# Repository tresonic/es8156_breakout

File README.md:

# ES8156 Breakout - *Untested*

Breakout PCB for the Everest Semiconductor [ES8156](http://www.everest-semi.com/pdf/ES8156%20PB.pdf), a DAC with integrated headphone driver.

----

Symbol and footprint were generated to `./lib` with [easyeda2kicad.py](https://github.com/uPesy/easyeda2kicad.py) like:

`easyeda2kicad --full --lcsc_id=C2887138 --output ./lib/lcsc_parts`

----

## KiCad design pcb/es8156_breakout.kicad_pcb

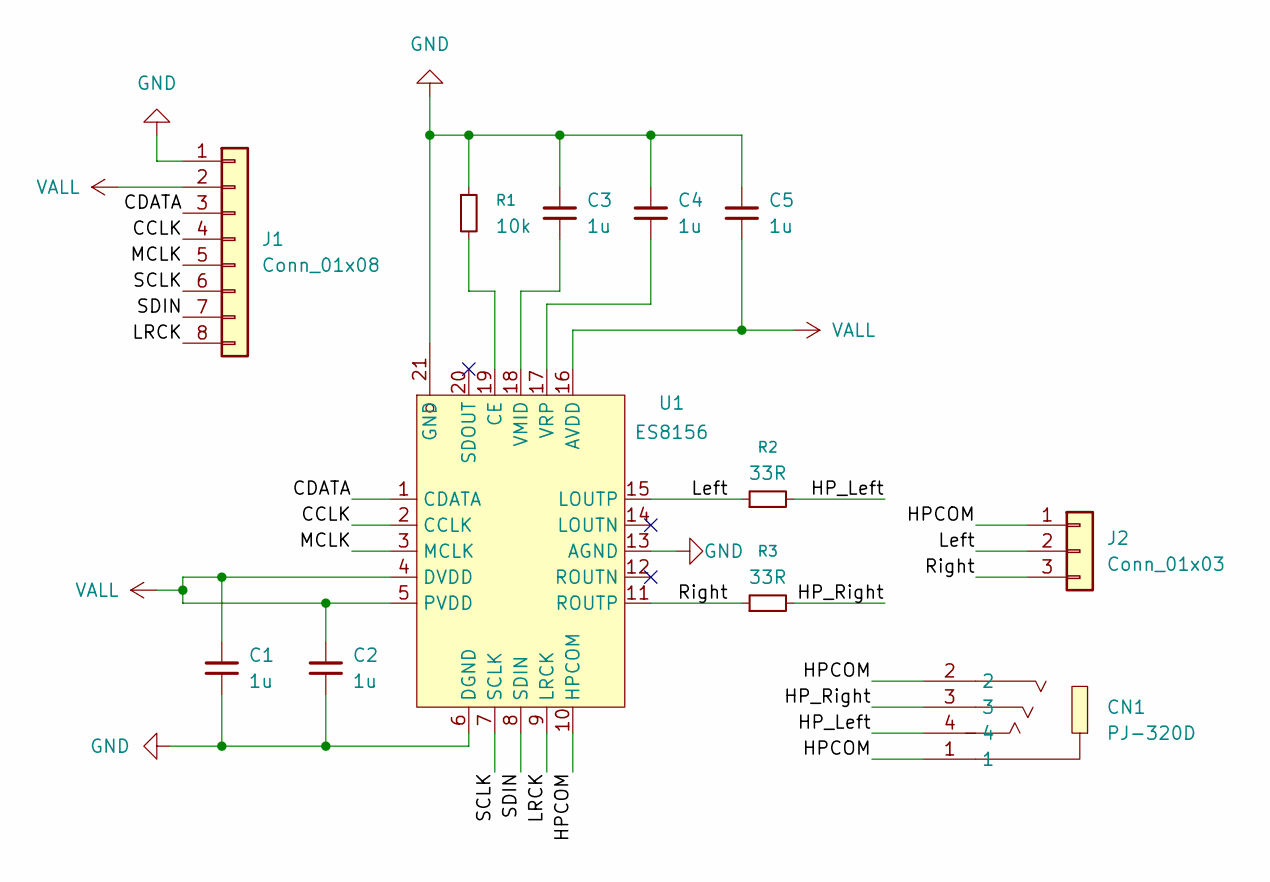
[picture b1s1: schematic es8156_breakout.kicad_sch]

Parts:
C1, C2, C3, C4, C5: 1u; C_0603_1608Metric_Pad1.08x0.95mm_HandSolder
CN1: PJ-320D; AUDIO-SMD_PJ-320D; LCSC Part C431535
J1: Conn_01x08; PinHeader_1x08_P2.54mm_Vertical
J2: Conn_01x03; PinHeader_1x03_P2.54mm_Vertical
R1: 10k; R_0603_1608Metric_Pad0.98x0.95mm_HandSolder
R2, R3: 33R; R_0603_1608Metric_Pad0.98x0.95mm_HandSolder
U1: ES8156; QFN-20_L3.0-W3.0-P0.40-TL-EP1.7; LCSC Part C2887138

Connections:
/CCLK: J1.4, U1.2 (CCLK)
/CDATA: J1.3, U1.1 (CDATA)
/HPCOM: CN1.1, CN1.2, J2.1, U1.10 (HPCOM)
/HP_Left: CN1.4, R2.2
/HP_Right: CN1.3, R3.2
/LRCK: J1.8, U1.9 (LRCK)
/Left: J2.2, R2.1, U1.15 (LOUTP)
/MCLK: J1.5, U1.3 (MCLK)
/Right: J2.3, R3.1, U1.11 (ROUTP)
/SCLK: J1.6, U1.7 (SCLK)
/SDIN: J1.7, U1.8 (SDIN)
GND: C1.2, C2.2, C3.1, C4.1, C5.1, J1.1, R1.1, U1.6 (DGND), U1.13 (AGND), U1.21 (GND)
unnamed: R1.2, U1.19 (CE)
unnamed: C3.2, U1.18 (VMID)
unnamed: C4.2, U1.17 (VRP)
VALL: C1.1, C2.1, C5.2, J1.2, U1.4 (DVDD), U1.5 (PVDD), U1.16 (AVDD)

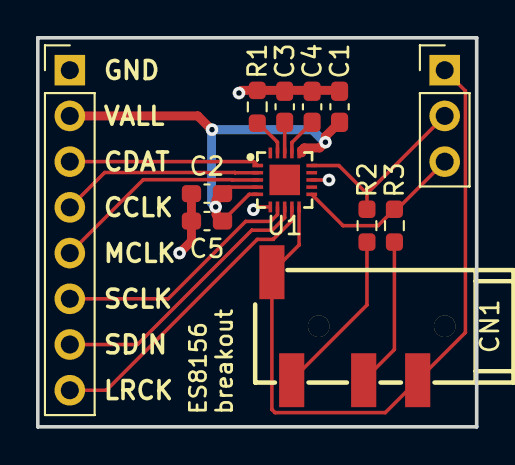
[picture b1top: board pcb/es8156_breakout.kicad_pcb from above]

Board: 2 copper layers, 24.4 x 21.6 mm, 12 parts (0 on the bottom side), 16 nets.

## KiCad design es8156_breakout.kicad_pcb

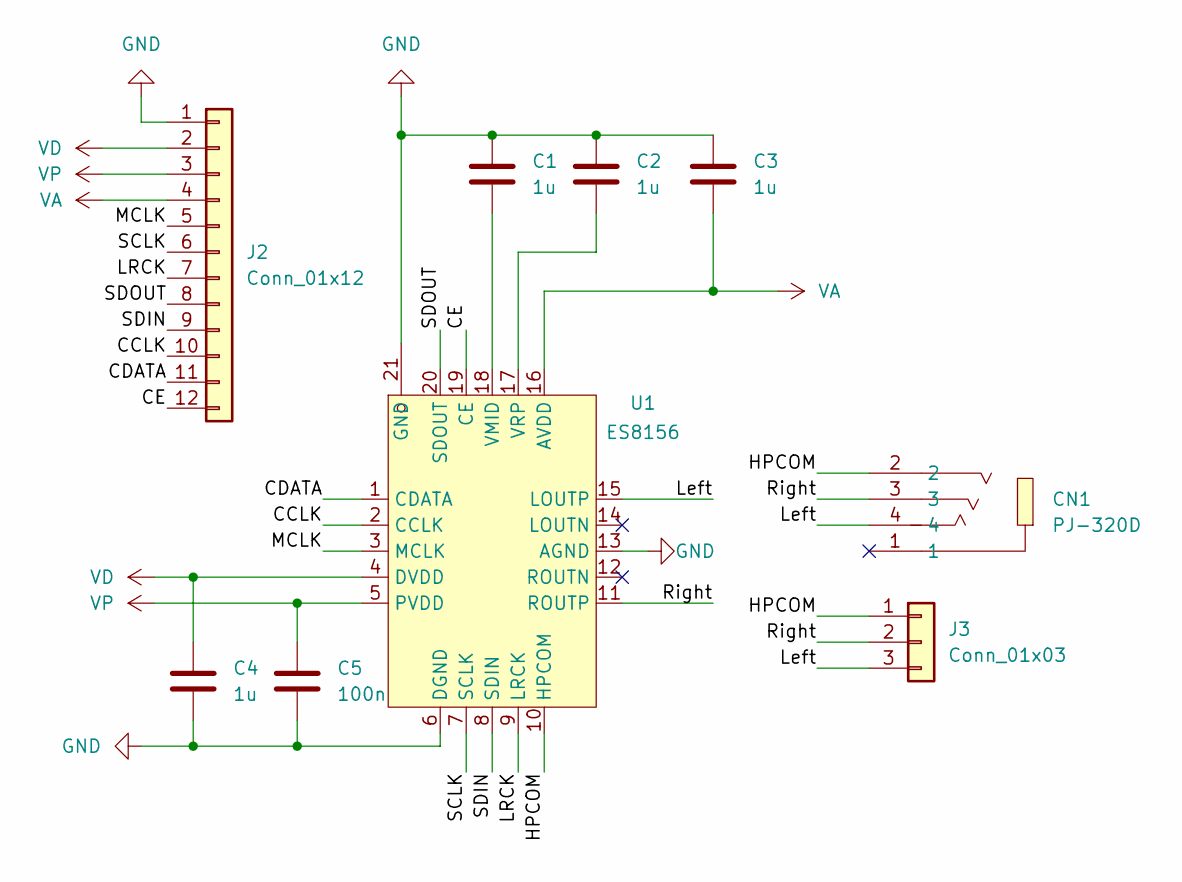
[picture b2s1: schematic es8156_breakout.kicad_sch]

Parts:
C1, C2, C3, C4: 1u; C_0603_1608Metric_Pad1.08x0.95mm_HandSolder
C5: 100n; C_0603_1608Metric_Pad1.08x0.95mm_HandSolder
CN1: PJ-320D; AUDIO-SMD_PJ-320D; LCSC Part C431535
J2: Conn_01x12; PinHeader_1x12_P2.54mm_Vertical
J3: Conn_01x03; PinHeader_1x03_P2.54mm_Vertical
U1: ES8156; QFN-20_L3.0-W3.0-P0.40-TL-EP1.7; LCSC Part C2887138

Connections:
/CCLK: J2.10, U1.2 (CCLK)
/CDATA: J2.11, U1.1 (CDATA)
/CE: J2.12, U1.19 (CE)
/HPCOM: CN1.2, J3.1, U1.10 (HPCOM)
/LRCK: J2.7, U1.9 (LRCK)
/Left: CN1.4, J3.3, U1.15 (LOUTP)
/MCLK: J2.5, U1.3 (MCLK)
/Right: CN1.3, J3.2, U1.11 (ROUTP)
/SCLK: J2.6, U1.7 (SCLK)
/SDIN: J2.9, U1.8 (SDIN)
/SDOUT: J2.8, U1.20 (SDOUT)
GND: C1.1, C2.1, C3.1, C4.2, C5.2, J2.1, U1.6 (DGND), U1.13 (AGND), U1.21 (GND)
unnamed: C1.2, U1.18 (VMID)
unnamed: C2.2, U1.17 (VRP)
VA: C3.2, J2.4, U1.16 (AVDD)
VD: C4.1, J2.2, U1.4 (DVDD)
VP: C5.1, J2.3, U1.5 (PVDD)

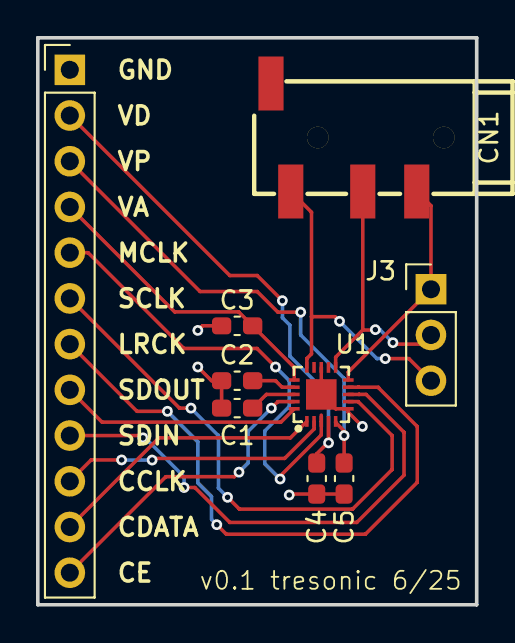
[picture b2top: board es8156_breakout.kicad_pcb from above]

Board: 2 copper layers, 24.4 x 31.5 mm, 9 parts (0 on the bottom side), 17 nets.

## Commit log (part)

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2025-06-06 init
2025-06-06 silkscreen adjustments
2025-06-06 use lcsc imported audio jack
2025-06-06 small adjustments
2026-04-21 move pcb into subfolder
2026-04-21 add driver code to test
